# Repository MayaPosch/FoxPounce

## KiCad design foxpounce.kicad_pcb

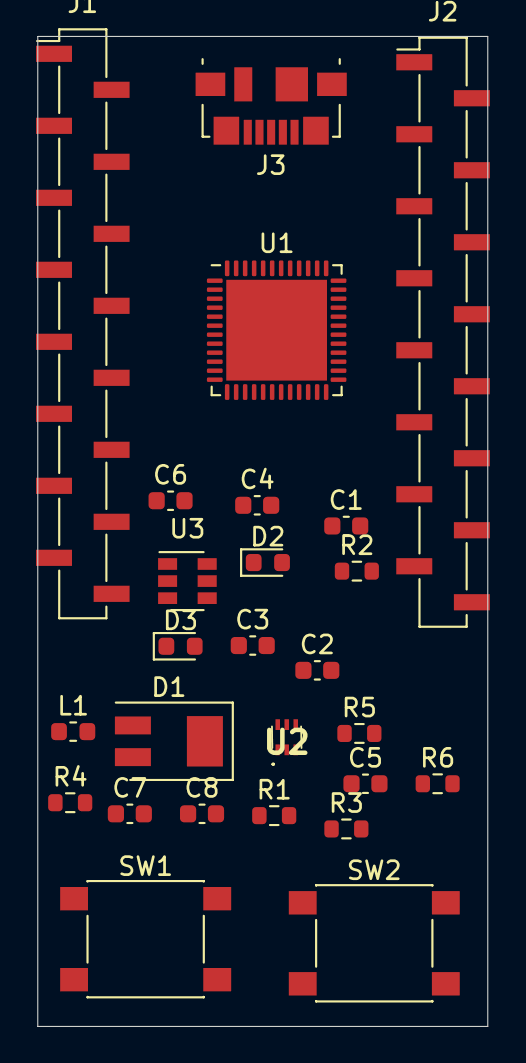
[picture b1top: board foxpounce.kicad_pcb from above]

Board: 2 copper layers, 25.0 x 55.0 mm, 27 parts (1 on the bottom side), 17 nets, no tracks yet.

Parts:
BT1: Battery_Cell; BatteryHolder_Keystone_1058_1x2032
C1, C2, C3, C4, C7, C8: 100nF; C_0603_1608Metric
C5, C6: 10uF; C_0603_1608Metric
D1: D_Schottky_x2_Serial_AKC; D_SMB_Modified
D2, D3: LED_Small; LED_0603_1608Metric
J1, J2: Conn_01x16; PinSocket_1x16_P2.00mm_Vertical_SMD_Pin1Left
J3: USB_OTG; USB_Micro-B_Molex_47346-0001
L1: 1 uH; L_0603_1608Metric
R1, R2, R3, R4, R5, R6: 10k; R_0603_1608Metric
SW1, SW2: SW_Push; SW_Push_1P1T_NO_6x6mm_H9.5mm
U1: STM32F412CGUx; QFN-48-1EP_7x7mm_P0.5mm_EP5.6x5.6mm
U2: MP2151GTF-33-P; MP2151GTF33P
U3: USBLC6-2SC6; SOT-23-6

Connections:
+3.3VA: C2.1, U1.9
+3V3: C1.1, C6.1, D1.2, L1.2, R3.2, R4.2, SW1.2, U1.24, U1.36, U1.48, U2.6
BOOT0: R1.2, SW1.1, U1.44
GND: BT1.2, C1.2, C3.1, C4.1, C5.1, C6.2, C7.1, C8.2, D2.1, D3.1, J1.12, J2.2, J3.5, J3.6, R1.1, R2.1, SW2.2, U1.23, U1.35, U1.47, U1.49, U2.1, U3.2
GNDA: C2.2, C7.2, U1.8
NRST: C3.2, R3.1, SW2.1, U1.7
unnamed: BT1.1, U1.1
unnamed: D2.2, R4.1
unnamed: D3.2, R5.1
unnamed: L1.1, U2.2
PB2: R2.2, U1.20
PC13: R5.2, U1.2
PWR_GD: R6.1, U2.5
USB_D+: J3.3, U3.3
USB_D-: J3.2, U3.1
VBAT: C4.2, D1.3
VBUS: C5.2, C8.1, J2.1, J3.1, R6.2, U2.3, U3.5

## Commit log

2021-01-23 Initial commit. WIP.
